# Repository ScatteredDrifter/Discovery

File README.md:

# Discovery

A bluetooth unibody splitkeyboard

---

### Current Status:

- PCB might be conceptualized soon

---

Discovery was yet another spaceshuttle flewn by NASA for their supply and repair schedules surrounding the orbit and ISS.  

---

## Features:
- Layout:

---

## Images:

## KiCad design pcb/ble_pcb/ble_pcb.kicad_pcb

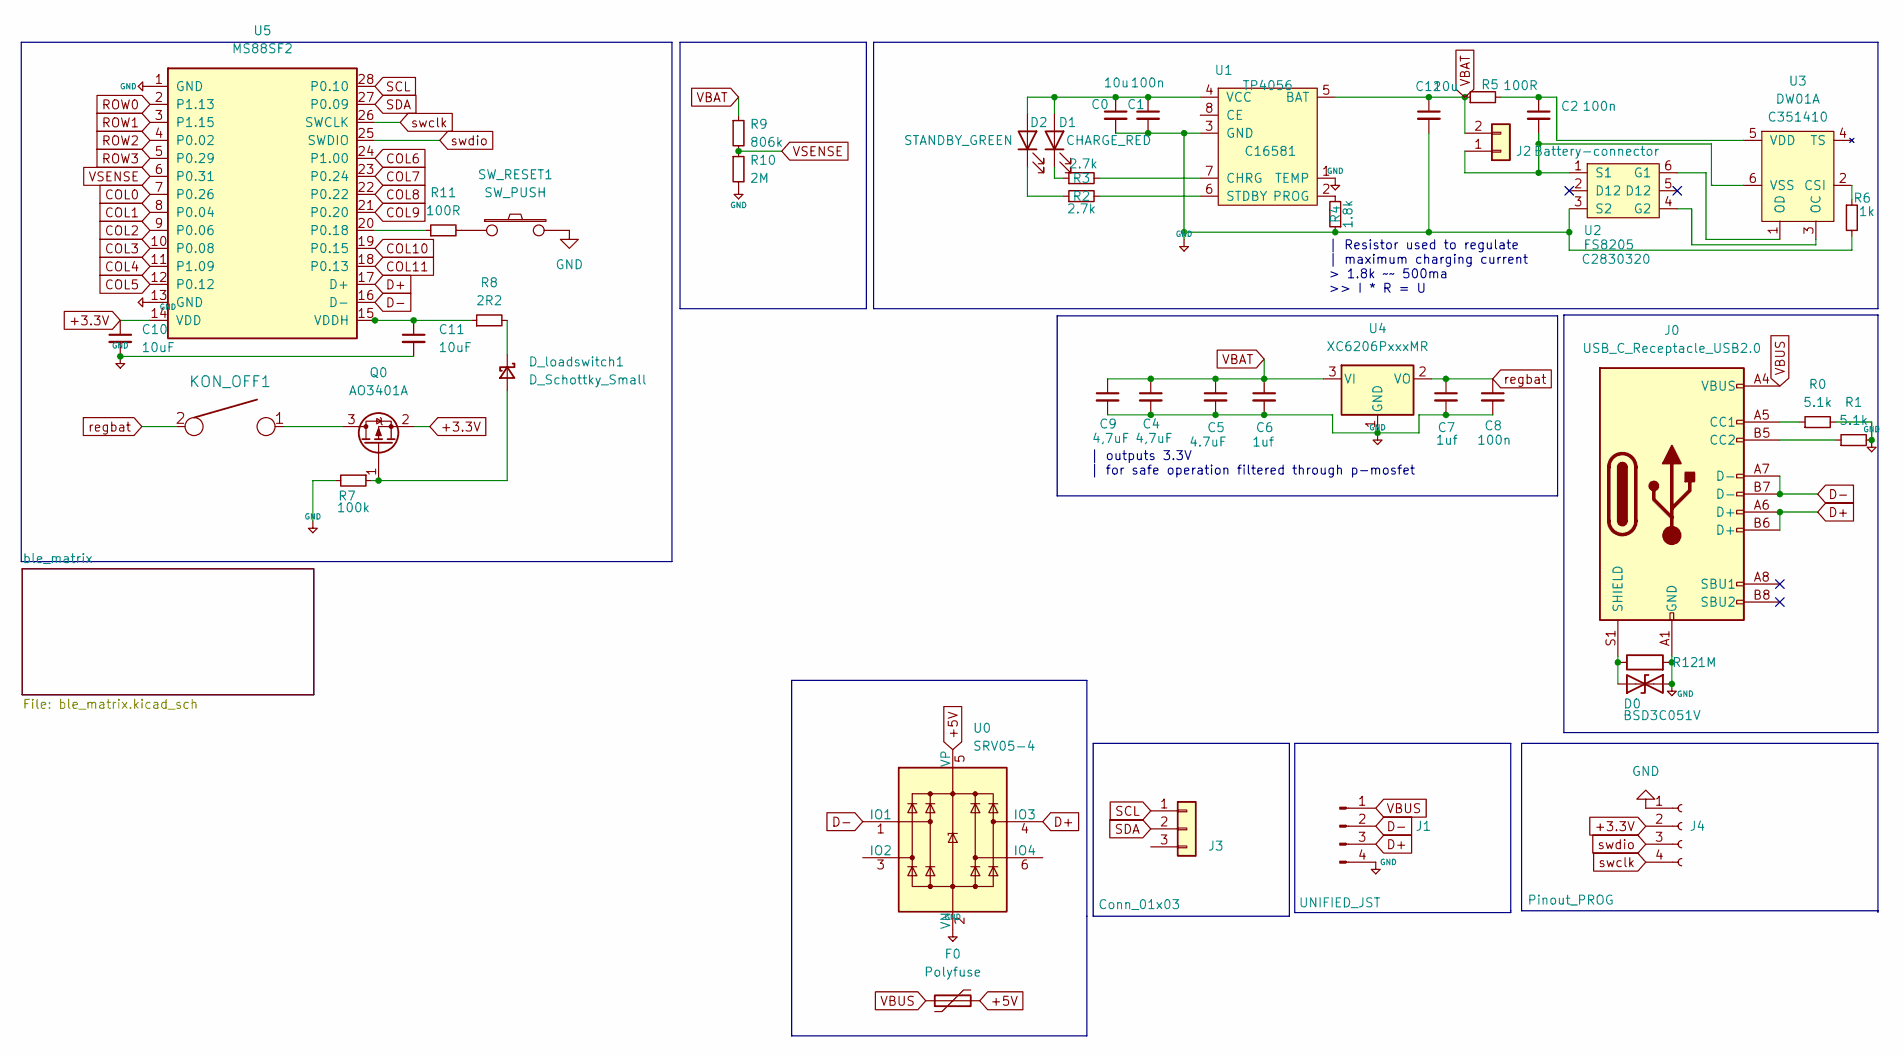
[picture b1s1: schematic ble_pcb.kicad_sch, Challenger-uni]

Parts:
C0, C12: 10u; C_0805_2012Metric; LCSC C15850
C1, C2, C8: 100n; C_0805_2012Metric; LCSC C49678
C4, C9: 4,7uF; C_0805_2012Metric; LCSC C1779
C5: 4.7uF; C_0805_2012Metric; LCSC C1779
C6, C7: 1uf; C_0805_2012Metric; LCSC C28323
C10, C11: 10uF; C_0805_2012Metric; LCSC C15850
D0: BSD3C051V; D_DO-201AE_P15.24mm_Horizontal; LCSC C151996
D1: CHARGE_RED; D_0805_2012Metric; LCSC C84256
D2: STANDBY_GREEN; D_0805_2012Metric; LCSC C2297
D_loadswitch1: D_Schottky_Small; D_SOD-323_HandSoldering; LCSC C172430
F0: Polyfuse; Fuse_0603_1608Metric; LCSC C69688
J0: USB_C_Receptacle_USB2.0; USB_C_Receptacle_HRO_TYPE-C-31-M-12; LCSC C165948
J1: UNIFIED_JST; Aio3_jst; LCSC C2845363
J2: Battery-connector; Molex PicoBlade 2Pin smt tht
J3: Conn_01x03; PinHeader_1x04_P2.54mm_Vertical
J4: Pinout_PROG; PinHeader_1x04_P2.54mm_Vertical
KON_OFF1: KEYSW; K3-2380S-E1 On-on
Q0: AO3401A; SOT-23; LCSC C15127
R0, R1: 5.1k; R_0815_2038Metric; LCSC C27834
R2, R3: 2.7k; R_0815_2038Metric; LCSC C2907305
R4: 1.8k; R_0815_2038Metric; LCSC C2907292
R5, R11: 100R; R_0815_2038Metric; LCSC C17408
R6: 1k; R_0815_2038Metric; LCSC C17513
R7: 100k; R_0815_2038Metric; LCSC C149504
R8: 2R2; R_0815_2038Metric; LCSC C17521
R9: 806k; R_0815_2038Metric; LCSC C63494
R10: 2M; R_0815_2038Metric; LCSC C26112
R12: 1M; R_0815_2038Metric; LCSC C17514
SW_RESET1: SW_PUSH; SW_SPST_TL3342; LCSC C318884
U0: SRV05-4; SOT-23-6; LCSC C85364
U1: TP4056; TP4056_SOP-8-PP; LCSC C16581
U2: FS8205; SOT-23-6; LCSC C2830320
U3: DW01A; SOT-23-6; LCSC C351410
U4: XC6206PxxxMR; SOT-23; LCSC C5446
U5: MS88SF2

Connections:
+3.3V: C10.1, J4.2, Q0.2 (S), U5.14 (VDD)
COL0: U5.7 (P0.26); also elsewhere on the board
COL1: U5.8 (P0.04); also elsewhere on the board
COL2: U5.9 (P0.06); also elsewhere on the board
COL3: U5.10 (P0.08); also elsewhere on the board
COL4: U5.11 (P1.09); also elsewhere on the board
COL5: U5.12 (P0.12); also elsewhere on the board
COL6: U5.24 (P1.00); also elsewhere on the board
COL7: U5.23 (P0.24); also elsewhere on the board
COL8: U5.22 (P0.22); also elsewhere on the board
COL9: U5.21 (P0.20); also elsewhere on the board
COL10: U5.19 (P0.15); also elsewhere on the board
COL11: U5.18 (P0.13); also elsewhere on the board
D+: J0.A6 (D+), J0.B6 (D+), J1.3, U0.4 (IO3), U5.17 (D+)
D-: J0.A7 (D-), J0.B7 (D-), J1.2, U0.1 (IO1), U5.16 (D-)
unnamed: C0.1, C1.1, D1.2 (A), D2.2 (A), U1.4 (VCC)
unnamed: C2.1, R5.2, U3.5 (VDD)
unnamed: C2.2, J2.1, U2.1 (S1), U3.6 (VSS)
unnamed: C4.1, C5.1, C6.1, C9.1, U4.3 (VI)
unnamed: C11.1, R8.1, U5.15 (VDDH)
unnamed: D0.1 (A1), J0.S1 (SHIELD), R12.1
unnamed: D1.1 (K), R3.1
unnamed: D2.1 (K), R2.1
unnamed: D_loadswitch1.1 (K), R8.2
unnamed: D_loadswitch1.2 (A), Q0.1 (G), R7.1
unnamed: J0.A5 (CC1), R0.1
unnamed: J0.B5 (CC2), R1.1
unnamed: KON_OFF1.1, Q0.3 (D)
unnamed: R2.2, U1.6 (STDBY)
unnamed: R3.2, U1.7 (CHRG)
unnamed: R4.2, U1.2 (PROG)
unnamed: R6.1, U3.2 (CSI)
unnamed: R11.1, U5.20 (P0.18)
unnamed: R11.2, SW_RESET1.1
unnamed: U2.4 (G2), U3.3 (OC)
unnamed: U2.6 (G1), U3.1 (OD)
ROW0: U5.2 (P1.13); also elsewhere on the board
ROW1: U5.3 (P1.15); also elsewhere on the board
ROW2: U5.4 (P0.02); also elsewhere on the board
ROW3: U5.5 (P0.29); also elsewhere on the board
SCL: J3.1, U5.28 (P0.10)
SDA: J3.2, U5.27 (P0.09)
VBAT: C12.1, J2.2, R5.1, R9.1, U1.5 (BAT)
VBUS: F0.1, J0.A4 (VBUS), J0.A9 (VBUS), J0.B4 (VBUS), J0.B9 (VBUS), J1.1
VSENSE: R9.2, R10.1, U5.6 (P0.31)
regbat: C7.1, C8.1, KON_OFF1.2, U4.2 (VO)
swclk: J4.4, U5.26 (SWCLK)
swdio: J4.3, U5.25 (SWDIO)

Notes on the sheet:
| outputs 3.3V | for safe operation filtered through p-mosfet
| Resistor used to regulate | maximum charging current > 1.8k ~~ 500ma >> I * R = U

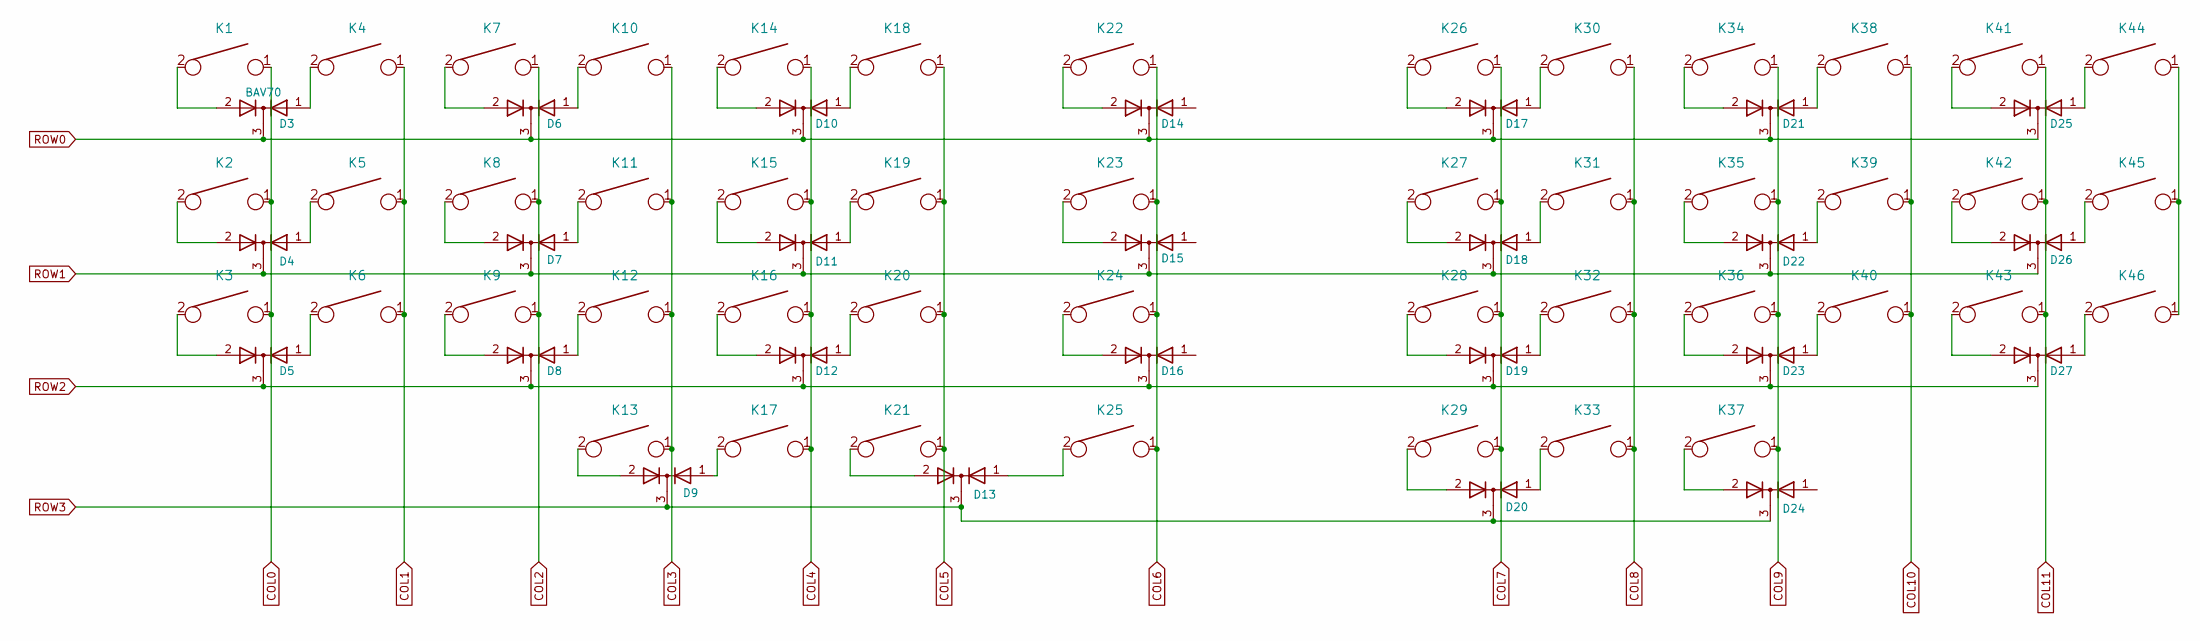
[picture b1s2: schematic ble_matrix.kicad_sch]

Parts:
D3: BAV70; SOT-23
D4, D5, D6, D7, D8, D9, D10, D11, D12, D13, D14, D15, D16, D17, D18, D19, D20, D21, D22, D23, D24, D25, D26, D27: (no value)
K1: KEYSW
K2, K3, K4, K5, K6, K7, K8, K9, K10, K11, K12, K13, K14, K15, K16, K17, K18, K19, K20, K21, K22, K23, K24, K25, K26, K27, K28, K29, K30, K31, K32, K33, K34, K35, K36, K37, K38, K39, K40, K41, K42, K43, K44, K45, K46: (no value)

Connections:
COL0: K1.1, K2.1, K3.1; also elsewhere on the board
COL1: K4.1, K5.1, K6.1; also elsewhere on the board
COL2: K7.1, K8.1, K9.1; also elsewhere on the board
COL3: K10.1, K11.1, K12.1, K13.1; also elsewhere on the board
COL4: K14.1, K15.1, K16.1, K17.1; also elsewhere on the board
COL5: K18.1, K19.1, K20.1, K21.1; also elsewhere on the board
COL6: K22.1, K23.1, K24.1, K25.1; also elsewhere on the board
COL7: K26.1, K27.1, K28.1, K29.1; also elsewhere on the board
COL8: K30.1, K31.1, K32.1, K33.1; also elsewhere on the board
COL9: K34.1, K35.1, K36.1, K37.1; also elsewhere on the board
COL10: K38.1, K39.1, K40.1; also elsewhere on the board
COL11: K41.1, K42.1, K43.1; also elsewhere on the board
unnamed: D3.1 (A), K4.2
unnamed: D3.2 (A), K1.2
unnamed: D4.1 (A), K5.2
unnamed: D4.2 (A), K2.2
unnamed: D5.1 (A), K6.2
unnamed: D5.2 (A), K3.2
unnamed: D6.1 (A), K10.2
unnamed: D6.2 (A), K7.2
unnamed: D7.1 (A), K11.2
unnamed: D7.2 (A), K8.2
unnamed: D8.1 (A), K12.2
unnamed: D8.2 (A), K9.2
unnamed: D9.1 (A), K17.2
unnamed: D9.2 (A), K13.2
unnamed: D10.1 (A), K18.2
unnamed: D10.2 (A), K14.2
unnamed: D11.1 (A), K19.2
unnamed: D11.2 (A), K15.2
unnamed: D12.1 (A), K20.2
unnamed: D12.2 (A), K16.2
unnamed: D13.1 (A), K25.2
unnamed: D13.2 (A), K21.2
unnamed: D14.2 (A), K22.2
unnamed: D15.2 (A), K23.2
unnamed: D16.2 (A), K24.2
unnamed: D17.1 (A), K30.2
unnamed: D17.2 (A), K26.2
unnamed: D18.1 (A), K31.2
unnamed: D18.2 (A), K27.2
unnamed: D19.1 (A), K32.2
unnamed: D19.2 (A), K28.2
unnamed: D20.1 (A), K33.2
unnamed: D20.2 (A), K29.2
unnamed: D21.1 (A), K38.2
unnamed: D21.2 (A), K34.2
unnamed: D22.1 (A), K39.2
unnamed: D22.2 (A), K35.2
unnamed: D23.1 (A), K40.2
unnamed: D23.2 (A), K36.2
unnamed: D24.2 (A), K37.2
unnamed: D25.1 (A), K44.2
unnamed: D25.2 (A), K41.2
unnamed: D26.1 (A), K45.2
unnamed: D26.2 (A), K42.2
unnamed: D27.1 (A), K46.2
unnamed: D27.2 (A), K43.2
unnamed: K44.1, K45.1, K46.1
ROW0: D3.3 (K), D6.3 (K), D10.3 (K), D14.3 (K), D17.3 (K), D21.3 (K), D25.3 (K); also elsewhere on the board
ROW1: D4.3 (K), D7.3 (K), D11.3 (K), D15.3 (K), D18.3 (K), D22.3 (K), D26.3 (K); also elsewhere on the board
ROW2: D5.3 (K), D8.3 (K), D12.3 (K), D16.3 (K), D19.3 (K), D23.3 (K), D27.3 (K); also elsewhere on the board
ROW3: D9.3 (K), D13.3 (K), D20.3 (K), D24.3 (K); also elsewhere on the board

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
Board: 2 copper layers, 115 parts (0 on the bottom side), 97 nets, no tracks yet.

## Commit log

2022-04-24 first commit, basics of schematic
